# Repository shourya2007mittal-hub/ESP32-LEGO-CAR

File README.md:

# ESP32-LEGO-CAR

So I made a custom ESP32 chip based Car which is based on LEGO theme. I made the PCB on Kicad and the 3D designs were made on autodesk fusion. The board encludes 16 MB flash Storage, USB-C Connector,voltage regulator , battery charging IC , and 2 motor drives. 

## Features

- Base on custom ESP32 chip
- Design Inspired by LEGO
- Includes 4 Motor gears and recharable battery.

   ### Schematic

 ###  PCB Design

### 3D Render

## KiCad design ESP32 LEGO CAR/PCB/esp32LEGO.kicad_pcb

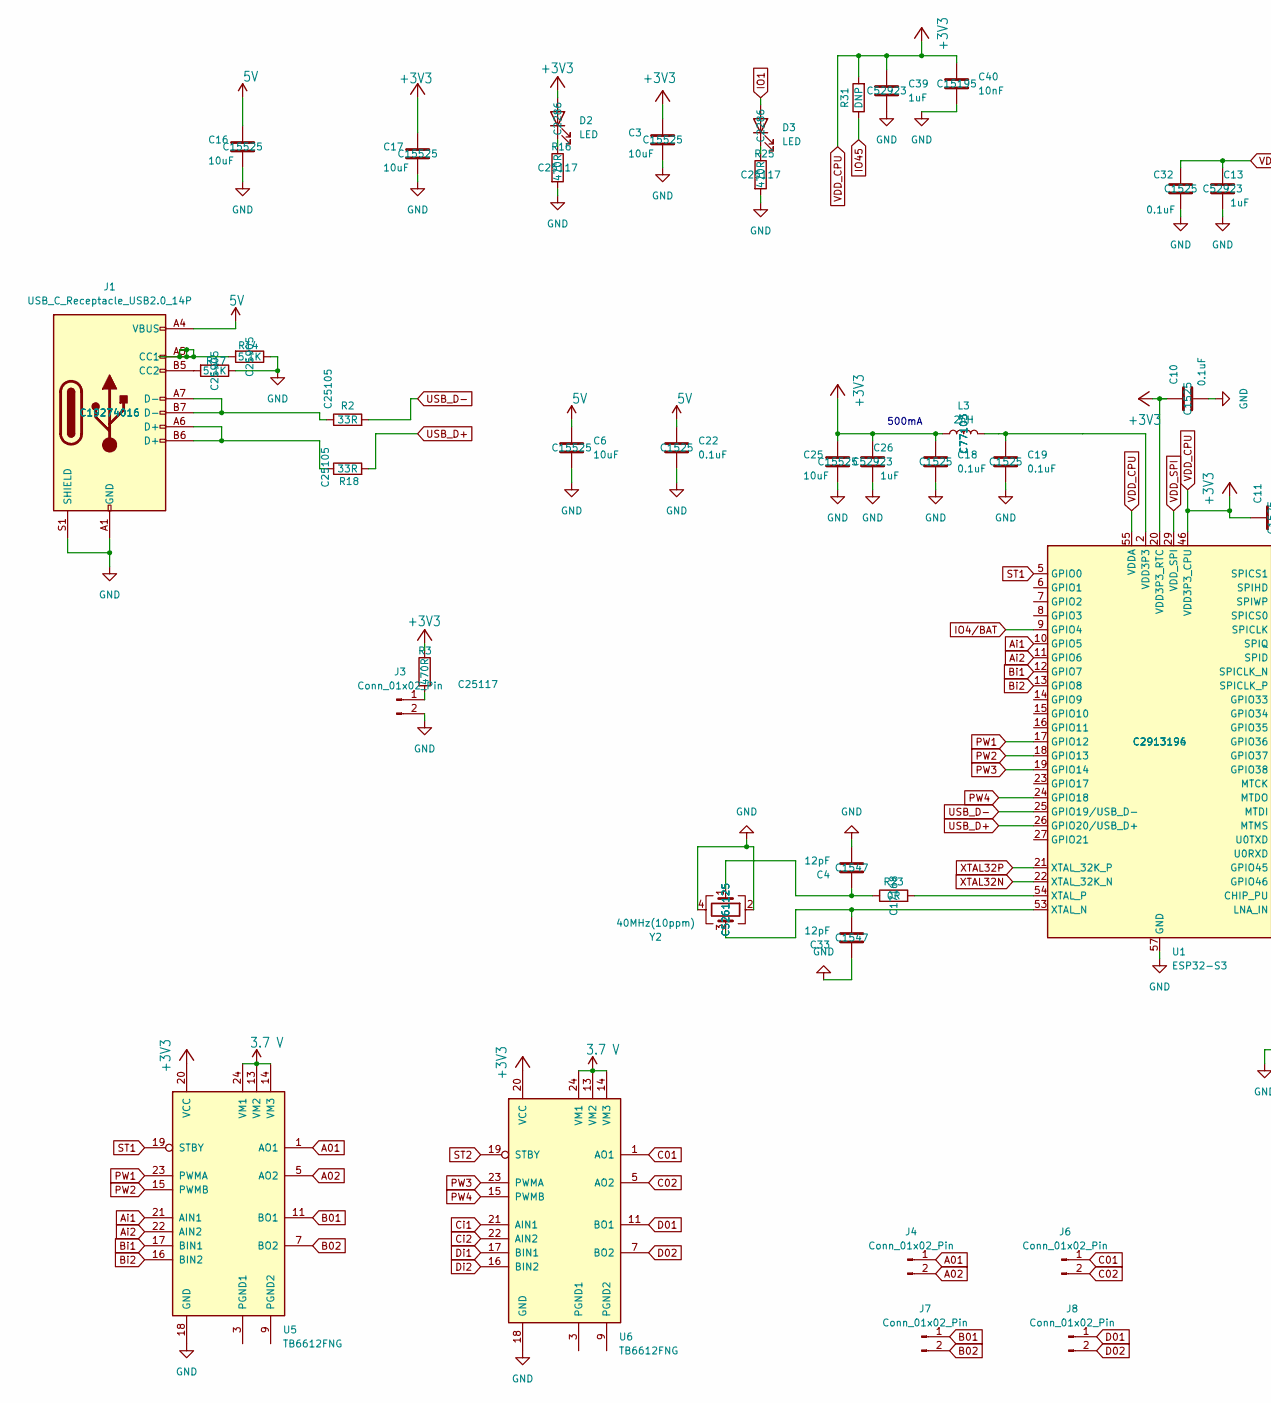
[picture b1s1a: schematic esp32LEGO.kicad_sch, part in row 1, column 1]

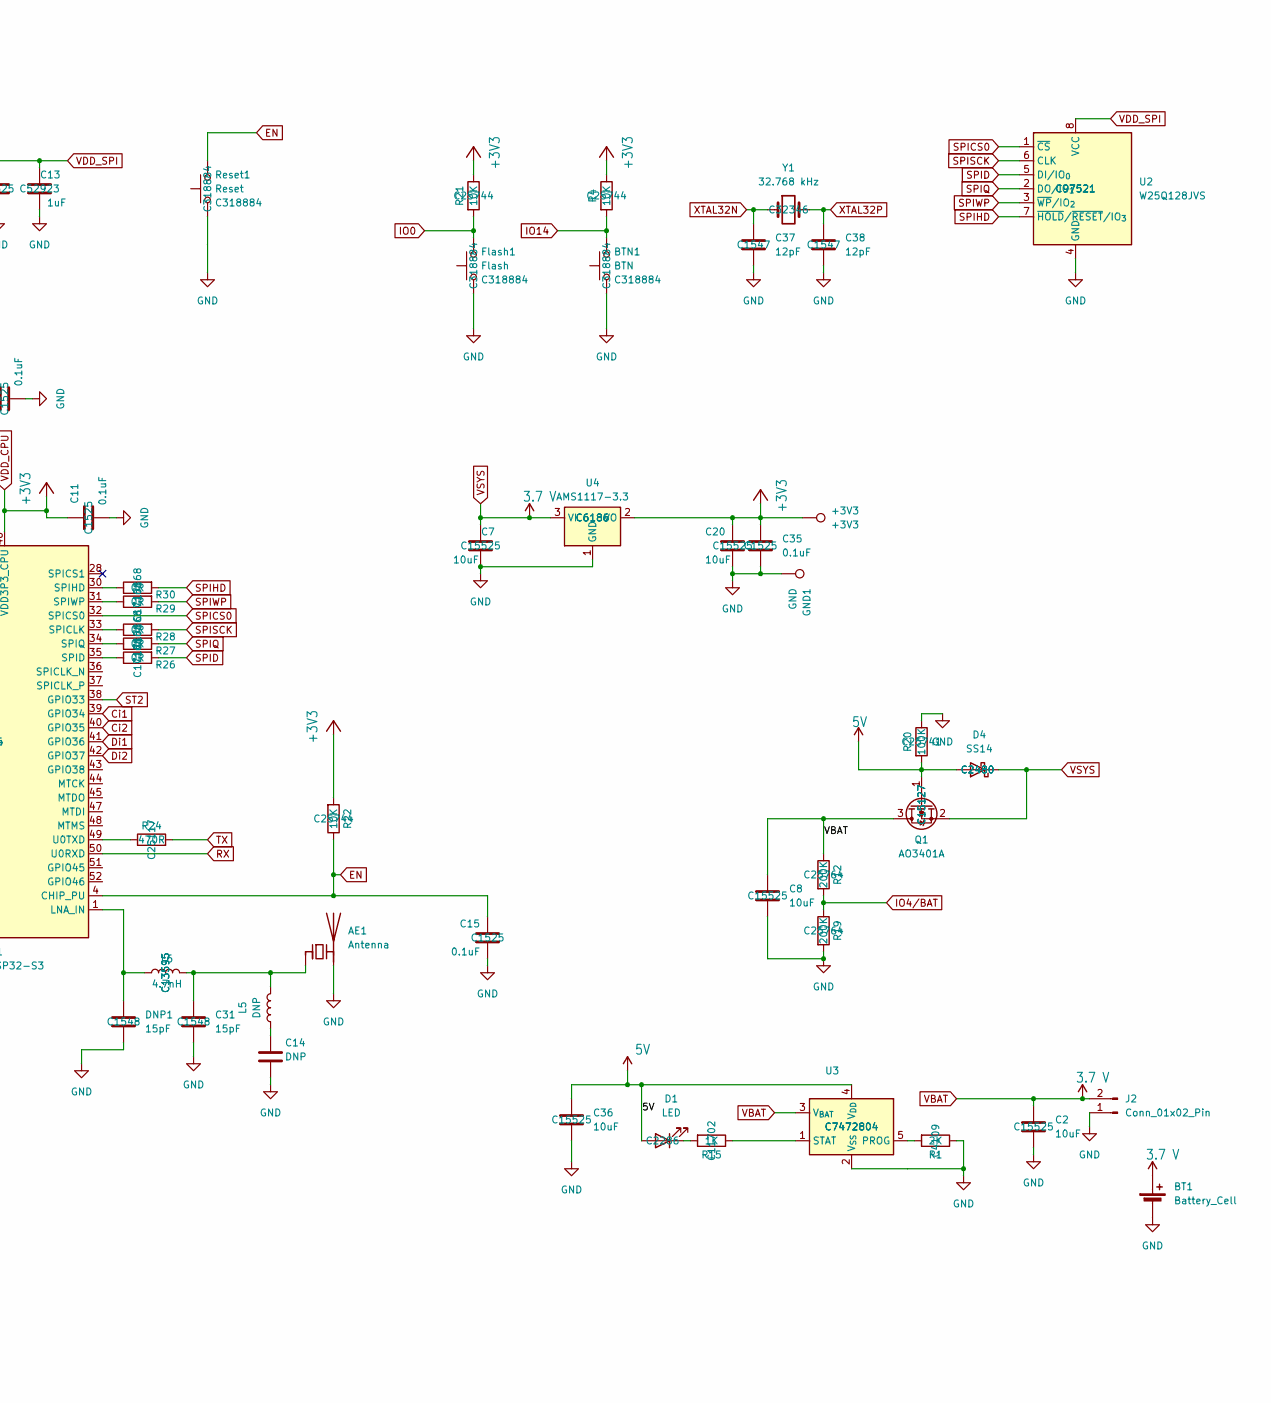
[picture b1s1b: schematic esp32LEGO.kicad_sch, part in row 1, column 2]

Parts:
+3V3: +3V3; TestPoint_Pad_D1.0mm
AE1: Antenna; Texas_SWRA117D_2.4GHz_Left
BT1: Battery_Cell
BTN1: BTN; SW_Push_1P1T_XKB_TS-1187A; MNF PART NUMBER C318884; LCSC C318884
C2, C3, C6, C7, C8, C16, C17, C20, C25, C36: 10uF; C_0402_1005Metric; MNF PART NUMBER C15525; LCSC C15525
C4, C33, C37, C38: 12pF; C_0402_1005Metric; MNF PART NUMBER C1547; LCSC C1547
C10, C11, C15, C18, C19, C22, C32, C35: 0.1uF; C_0402_1005Metric; MNF PART NUMBER C1525; LCSC C1525
C13, C26, C39: 1uF; C_0402_1005Metric; MNF PART NUMBER C52923; LCSC C52923
C14: DNP; C_0402_1005Metric
C31: 15pF; C_0402_1005Metric; MNF PART NUMBER C1548; LCSC C1548
C40: 10nF; C_0402_1005Metric; MNF PART NUMBER C15195; LCSC C15195
D1, D2, D3: LED; LED_0603_1608Metric; MNF PART NUMBER C2286; LCSC C2286
D4: SS14; D_SMA; MNF PART NUMBER C2480; LCSC C2480
DNP1: 15pF; C_0402_1005Metric; MNF PART NUMBER C1548; LCSC C1548
Flash1: Flash; SW_Push_1P1T_XKB_TS-1187A; MNF PART NUMBER C318884; LCSC C318884
GND1: GND; TestPoint_Pad_D1.0mm
J1: USB_C_Receptacle_USB2.0_14P; USB_C_Receptacle_HCTL_HC-TYPE-C-16P-01A; MNF PART NUMBER C19274016; LCSC C19274016
J2: Conn_01x02_Pin; PinSocket_1x02_P2.54mm_Vertical
J3, J4, J6, J7, J8: Conn_01x02_Pin; AMASS_XT30U-F_1x02_P5.0mm_Vertical
L3: 2nH; L_0402_1005Metric; MNF PART NUMBER C77103; LCSC C77103
L5: DNP; L_0402_1005Metric
L6: 4.7nH; L_0402_1005Metric; MNF PART NUMBER C13595; LCSC C13595
Q1: AO3401A; SOT-23; MNF PART NUMBER C15127; LCSC C15127
R1: 2K; R_0402_1005Metric; MNF PART NUMBER C4109; LCSC C4109
R2, R18: 33R; R_0402_1005Metric; MNF PART NUMBER C25105; LCSC C25105
R3, R16, R24, R25: 470R; R_0402_1005Metric; MNF PART NUMBER C25117; LCSC C25117
R4, R21, R22: 10K; R_0402_1005Metric; MNF PART NUMBER C25744; LCSC C25744
R12, R19: 200K; R_0402_1005Metric; MNF PART NUMBER C25764; LCSC C25764
R14, R17: 5.1K; R_0402_1005Metric; MNF PART NUMBER C25905; LCSC C25905
R15: 1K; R_0402_1005Metric; MNF PART NUMBER C11702; LCSC C11702
R20: 100K; R_0402_1005Metric; MNF PART NUMBER C25741; LCSC C25741
R23, R26, R27, R28, R29, R30: 0R; R_0402_1005Metric; MNF PART NUMBER C17168; LCSC C17168
R31: DNP; R_0402_1005Metric
Reset1: Reset; SW_Push_1P1T_XKB_TS-1187A; MNF PART NUMBER C318884; LCSC C318884
U1: ESP32-S3; QFN-56-1EP_7x7mm_P0.4mm_EP4x4mm; MNF PART NUMBER C2913196; LCSC C2913194
U2: W25Q128JVS; SOIC-8_5.3x5.3mm_P1.27mm; MNF PART NUMBER C97521; LCSC C97521
U3: MCP73831-2-OT; SOT-23-5; MNF PART NUMBER C7472804; LCSC C7472804
U4: AMS1117-3.3; SOT-223-3_TabPin2; MNF PART NUMBER C6186; LCSC C6186
U5, U6: TB6612FNG; SSOP-24_5.3x8.2mm_P0.65mm
Y1: 32.768 kHz; Crystal_SMD_3215-2Pin_3.2x1.5mm; MNF PART NUMBER C32346; LCSC C32346
Y2: 40MHz(10ppm); Crystal_SMD_2520-4Pin_2.5x2.0mm; MNF PART NUMBER C5261125; LCSC C5261125

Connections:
5V: C6.1, C16.1, C22.1, C36.1, D1.2 (A), D4.2 (A), J1.A4 (VBUS), J1.A9 (VBUS), J1.B4 (VBUS), J1.B9 (VBUS), Q1.1 (G), R20.2, U3.4 (V_{DD})
A01: J4.1, U5.1 (AO1), U5.2 (AO1)
A02: J4.2, U5.5 (AO2), U5.6 (AO2)
Ai1: U1.10 (GPIO5), U5.21 (AIN1)
Ai2: U1.11 (GPIO6), U5.22 (AIN2)
B01: J7.1, U5.11 (BO1), U5.12 (BO1)
B02: J7.2, U5.7 (BO2), U5.8 (BO2)
Bi1: U1.12 (GPIO7), U5.17 (BIN1)
Bi2: U1.13 (GPIO8), U5.16 (BIN2)
C01: J6.1, U6.1 (AO1), U6.2 (AO1)
C02: J6.2, U6.5 (AO2), U6.6 (AO2)
Ci1: U1.39 (GPIO34), U6.21 (AIN1)
Ci2: U1.40 (GPIO35), U6.22 (AIN2)
D01: J8.1, U6.11 (BO1), U6.12 (BO1)
D02: J8.2, U6.7 (BO2), U6.8 (BO2)
Di1: U1.41 (GPIO36), U6.17 (BIN1)
Di2: U1.42 (GPIO37), U6.16 (BIN2)
EN: C15.1, R22.1, Reset1.2, U1.4 (CHIP_PU)
GND: AE1.2 (PCB_Trace), BT1.2 (-), BTN1.1, C2.2, C3.2, C4.2, C6.2, C7.2, C8.2, C10.2, C11.2, C13.2, C14.2, C15.2, C16.2, C17.2, C18.2, C19.2, C20.2, C22.2, C25.2, C26.2, C31.2, C32.2, C33.1, C35.2, C36.2, C37.2, C38.2, C39.2, C40.2, DNP1.2, Flash1.1, GND1.1, J1.A1 (GND), J1.A12 (GND), J1.B1 (GND), J1.B12 (GND), J1.S1 (SHIELD), J2.1, J3.2, R1.1, R14.1, R16.2, R17.1, R19.2, R20.1, R25.2, Reset1.1, U1.57 (GND), U2.4 (GND), U3.2 (V_{SS}), U4.1 (GND), U5.18 (GND), U6.18 (GND), Y2.2, Y2.4
IO0: Flash1.2, R21.2
IO1: D3.2 (A)
IO4/BAT: R12.2, R19.1, U1.9 (GPIO4)
IO14: BTN1.2, R4.2
IO45: R31.1
unnamed: AE1.1 (FEED), C31.1, L5.2, L6.2
unnamed: C4.1, R23.1, Y2.1
unnamed: C14.1, L5.1
unnamed: C19.1, L3.2, U1.2 (VDD3P3), U1.3 (VDD3P3)
unnamed: D1.1 (K), R15.2
unnamed: D2.1 (K), R16.1
unnamed: D3.1 (K), R25.1
unnamed: J1.A5 (CC1), R14.2
unnamed: J1.B5 (CC2), R17.2
unnamed: J1.A6 (D+), J1.B6 (D+), R18.1
unnamed: J1.A7 (D-), J1.B7 (D-), R2.1
unnamed: J3.1, R3.2
unnamed: DNP1.1, L6.1, U1.1 (LNA_IN)
unnamed: R28.1, U1.33 (SPICLK)
unnamed: R26.1, U1.35 (SPID)
unnamed: R30.1, U1.30 (SPIHD)
unnamed: R27.1, U1.34 (SPIQ)
unnamed: R29.1, U1.31 (SPIWP)
unnamed: R24.1, U1.49 (U0TXD)
unnamed: C33.2, U1.53 (XTAL_N), Y2.3
unnamed: R23.2, U1.54 (XTAL_P)
unnamed: R1.2, U3.5 (PROG)
unnamed: R15.1, U3.1 (STAT)
unnamed: U5.3 (PGND1), U5.4 (PGND1)
unnamed: U5.9 (PGND2), U5.10 (PGND2)
unnamed: U6.3 (PGND1), U6.4 (PGND1)
unnamed: U6.9 (PGND2), U6.10 (PGND2)
PW1: U1.17 (GPIO12), U5.23 (PWMA)
PW2: U1.18 (GPIO13), U5.15 (PWMB)
PW3: U1.19 (GPIO14), U6.23 (PWMA)
PW4: U1.24 (GPIO18), U6.15 (PWMB)
RX: U1.50 (U0RXD)
SPICS0: U1.32 (SPICS0), U2.1 (~CS)
SPID: R26.2, U2.5 (DI/IO_{0})
SPIHD: R30.2, U2.7 (~HOLD/~RESET/IO_{3})
SPIQ: R27.2, U2.2 (DO/IO_{1})
SPISCK: R28.2, U2.6 (CLK)
SPIWP: R29.2, U2.3 (~WP/IO_{2})
ST1: U1.5 (GPIO0), U5.19 (STBY)
ST2: U1.38 (GPIO33), U6.19 (STBY)
TX: R24.2
USB_D+: R18.2, U1.26 (GPIO20/USB_D+)
USB_D-: R2.2, U1.25 (GPIO19/USB_D-)
VBAT: BT1.1 (+), C2.1, C7.1, C8.1, D4.1 (K), J2.2, Q1.2 (S), Q1.3 (D), R12.1, U3.3 (V_{BAT}), U4.3 (VI), U5.13 (VM2), U5.14 (VM3), U5.24 (VM1), U6.13 (VM2), U6.14 (VM3), U6.24 (VM1)
VDD_CPU: +3V3.1, C3.1, C10.1, C11.1, C17.1, C18.1, C20.1, C25.1, C26.1, C35.1, C39.1, C40.1, D2.2 (A), L3.1, R3.1, R4.1, R21.1, R22.2, R31.2, U1.20 (VDD3P3_RTC), U1.46 (VDD3P3_CPU), U1.55 (VDDA), U1.56 (VDDA), U4.2 (VO), U5.20 (VCC), U6.20 (VCC)
VDD_SPI: C13.1, C32.1, U1.29 (VDD_SPI), U2.8 (VCC)
XTAL32N: C37.1, U1.22 (XTAL_32K_N), Y1.1
XTAL32P: C38.1, U1.21 (XTAL_32K_P), Y1.2

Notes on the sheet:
500mA

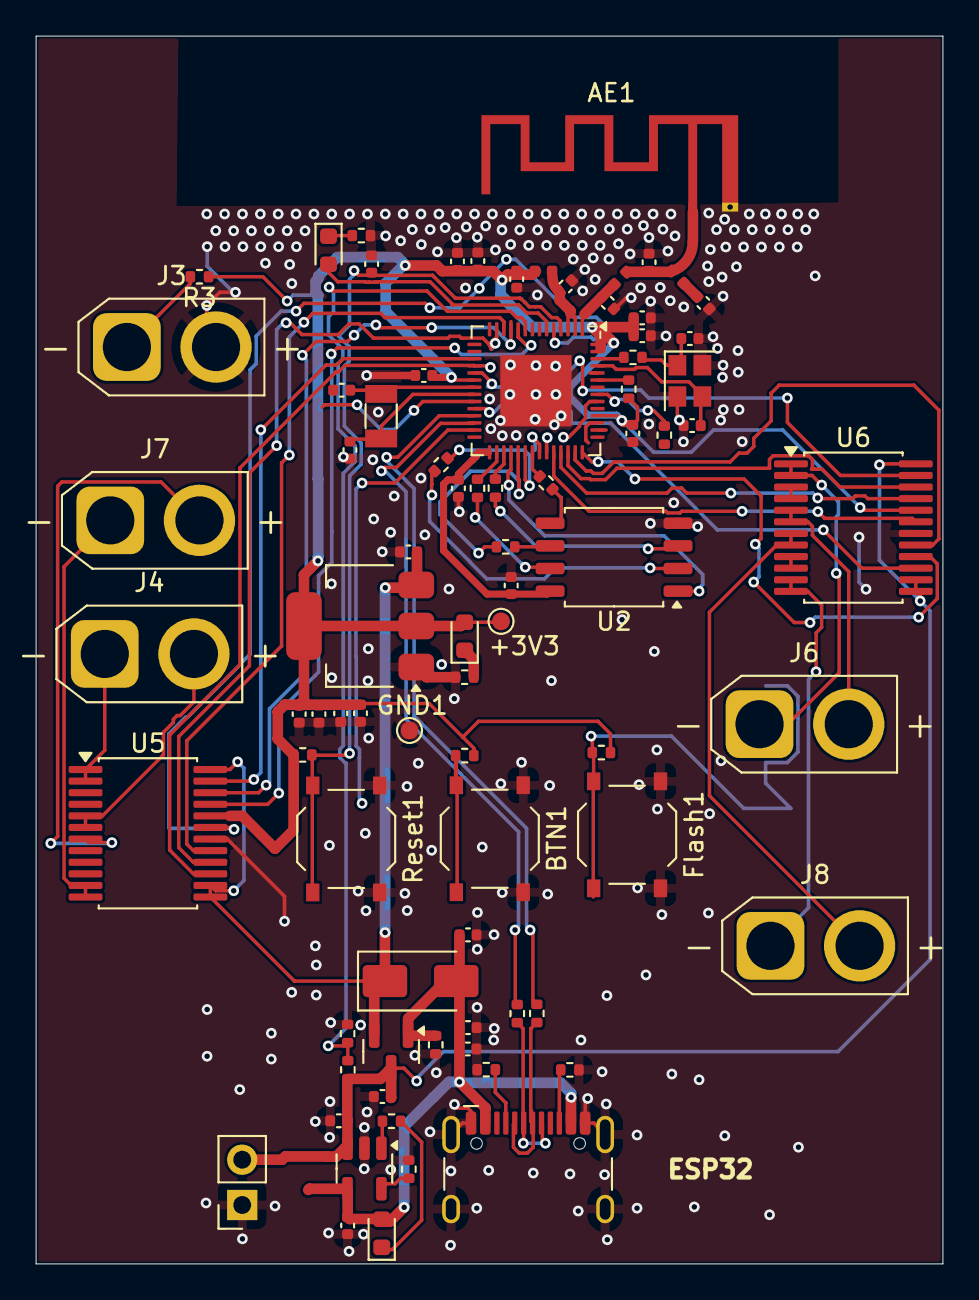
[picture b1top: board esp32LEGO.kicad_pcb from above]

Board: 2 copper layers, 50.9 x 68.8 mm, 81 parts (0 on the bottom side), 68 nets.
